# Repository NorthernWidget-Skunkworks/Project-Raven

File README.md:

# Project-Raven
Eagle designs for a high gain current amplifier board, for either bench-top or field use 

<br>
<br />This work is licensed under a <a rel="license" href="http://creativecommons.org/licenses/by-sa/4.0/">Creative Commons Attribution-ShareAlike 4.0 International License</a>.

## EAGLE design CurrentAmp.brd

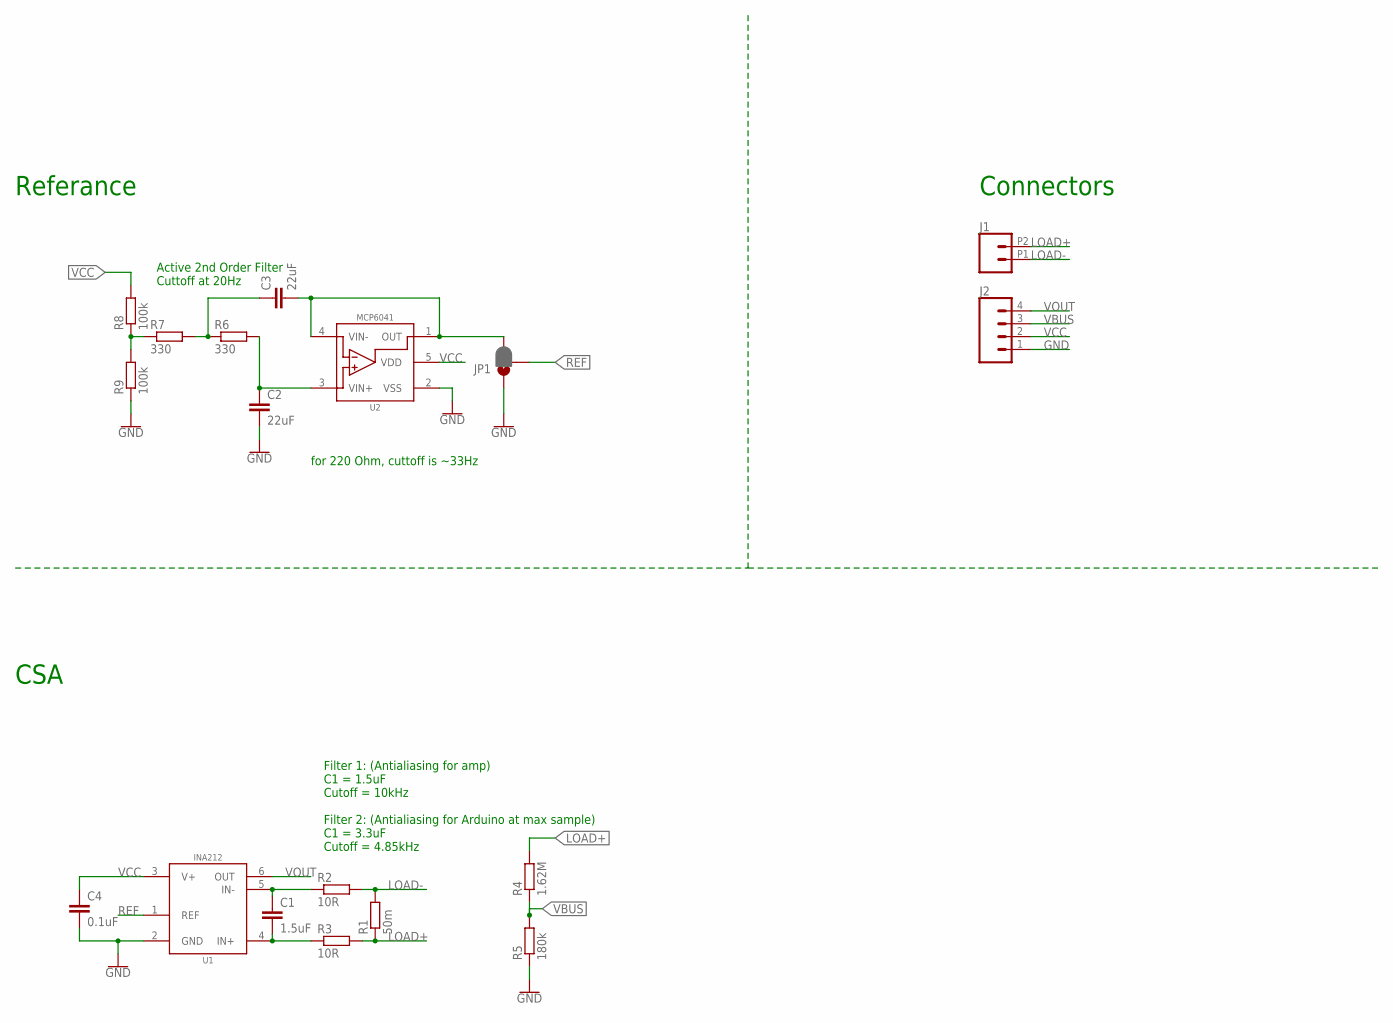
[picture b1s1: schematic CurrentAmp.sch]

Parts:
C1: 1.5uF; C0603
C2, C3: 22uF; C0805
C4: 0.1uF; C0603
J1: CONN_022.54MM_SCREWTERM; 1X02_2.54_SCREWTERM
J2: CONN_42.54_SCREW; 1X04_SCREW
JP1: JUMPER-SMT_3_1-NC_PASTE_SILK; SMT-JUMPER_3_1-NC_PASTE_SILK
R1: 50m; R0805
R2, R3: 10R; R0603
R4: 1.62M; R0603
R5: 180k; R0603
R6, R7: 330; R0603
R8, R9: 100k; R0603
U1: INA212DCK; DCK_R-PDSO-G6
U2: MCP6041; SOT23-5

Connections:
GND: C2.2, C4.2, J2.1, JP1.1, R5.1, R9.1, U1.2 (GND), U2.2 (VSS)
LOAD+: J1.P2 (2), R1.1, R3.2, R4.2
LOAD-: J1.P1 (1), R1.2, R2.2
unnamed: C1.1, R2.1, U1.5 (IN-)
unnamed: C1.2, R3.1, U1.4 (IN+)
unnamed: C3.2, JP1.3, U2.1 (OUT), U2.4 (VIN-)
unnamed: C2.1, R6.2, U2.3 (VIN+)
unnamed: C3.1, R6.1, R7.2
unnamed: R7.1, R8.1, R9.2
REF: JP1.2, U1.1 (REF)
VBUS: J2.3, R4.1, R5.2
VCC: C4.1, J2.2, R8.2, U1.3 (V+), U2.5 (VDD)
VOUT: J2.4, U1.6 (OUT)

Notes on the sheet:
Filter 1: (Antialiasing for amp) C1 = 1.5uF Cutoff = 10kHz Filter 2: (Antialiasing for Arduino at max sample) C1 = 3.3uF Cutoff = 4.85kHz
Active 2nd Order Filter Cuttoff at 20Hz
CSA
Referance
Connectors
for 220 Ohm, cuttoff is ~33Hz

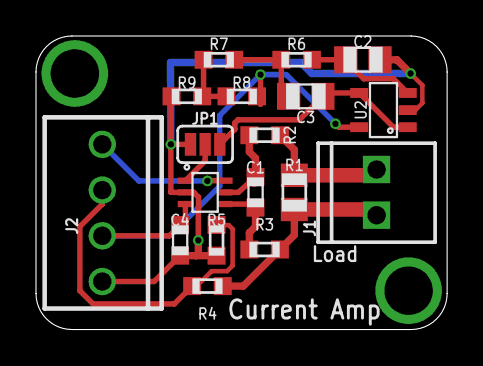
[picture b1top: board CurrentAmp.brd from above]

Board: 2 copper layers, 22.8 x 16.3 mm, 18 parts (0 on the bottom side), 13 nets.

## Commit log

2018-02-28 Initial commit
    Initial commit containing board file, schematic, as well as the gerber files used for the first order of these boards
2018-11-12 Minor schematic cleanup
2018-11-12 Schematic cleanup, added PDFs
2018-12-18 CC-BY-SA
2019-07-26 Added BoM and cleaned up part ID info on board

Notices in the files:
parts and their libraries:
SparkFun-Connectors: Licensing: Creative Commons ShareAlike 4.0 International - https://creativecommons.org/licenses/by-sa/4.0
bschulz: This work is licensed under the Creative Commons Attribution-ShareAlike 4.0
